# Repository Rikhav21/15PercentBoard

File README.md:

# Fifteen percent
## About
I called a fifteen percent keyboard, because it has only 32 keys in total, which is around thirty percent of a regular keyboard. Since it is a split keyboard, each *board* has around fifteen keys. I also made it as a grid, because those are supposedly better according to this one friend that I have but it is going to take like 3-4 weeks to adjust so have fun with relearning how to type!
## CAD
There is nothing really special about this, there is only a lid, and base for each. I am thinking of printing these in green, and in my opinion the renderings look pretty cool. They should be able to fit on my A1 mini, which is part of the reason why I made a split board in the first place.

## Schematic
Once again there is nothing really special. There are just the keys connected to a pico, according to rows, and columns. The picos are connected through a TRRS cable, and the right one, has a 0.96 inch OLED. I am going to have to see where I can get the TRRS cable connectors for cheaper, as right now thhe plugs seem way to overprices at 8 dollars per.

## PCB
This is just a simple PCB, I designed in Kicad.  I have all of the files in the github repo, and I am not really good at PCB design, it was my second time, which is partially why the routes are not really clean. However I do feel proud of it because it is pretty complex and I had to redo it like 3 times, and I only have 15 percent of the necassery keys.

## Firmware
I spent way to long making the firmware, because I was trying to map out the entire keyboard in my head, however this is only a standin for some better firmware later. After I actually build the board I am thinking of adding a bit more functionality, where pressing the 6 side keys could all have some cool function, and hte OLED would display what mode it was in, but for now th efirmwayre is still pretty basic until I actually make the thing.
## Matierials.
For this I will need some
- screws (m3) around 15mm
- heatset inserts m3x4x5
- Cerry MX, PCB mount keys (I want the really clicky jade ones.)
- keycaps 
- 2 raspberry picos
- 0.96 inch OLED
- Pin headers
- TRRS cable
- TRRS connectors.

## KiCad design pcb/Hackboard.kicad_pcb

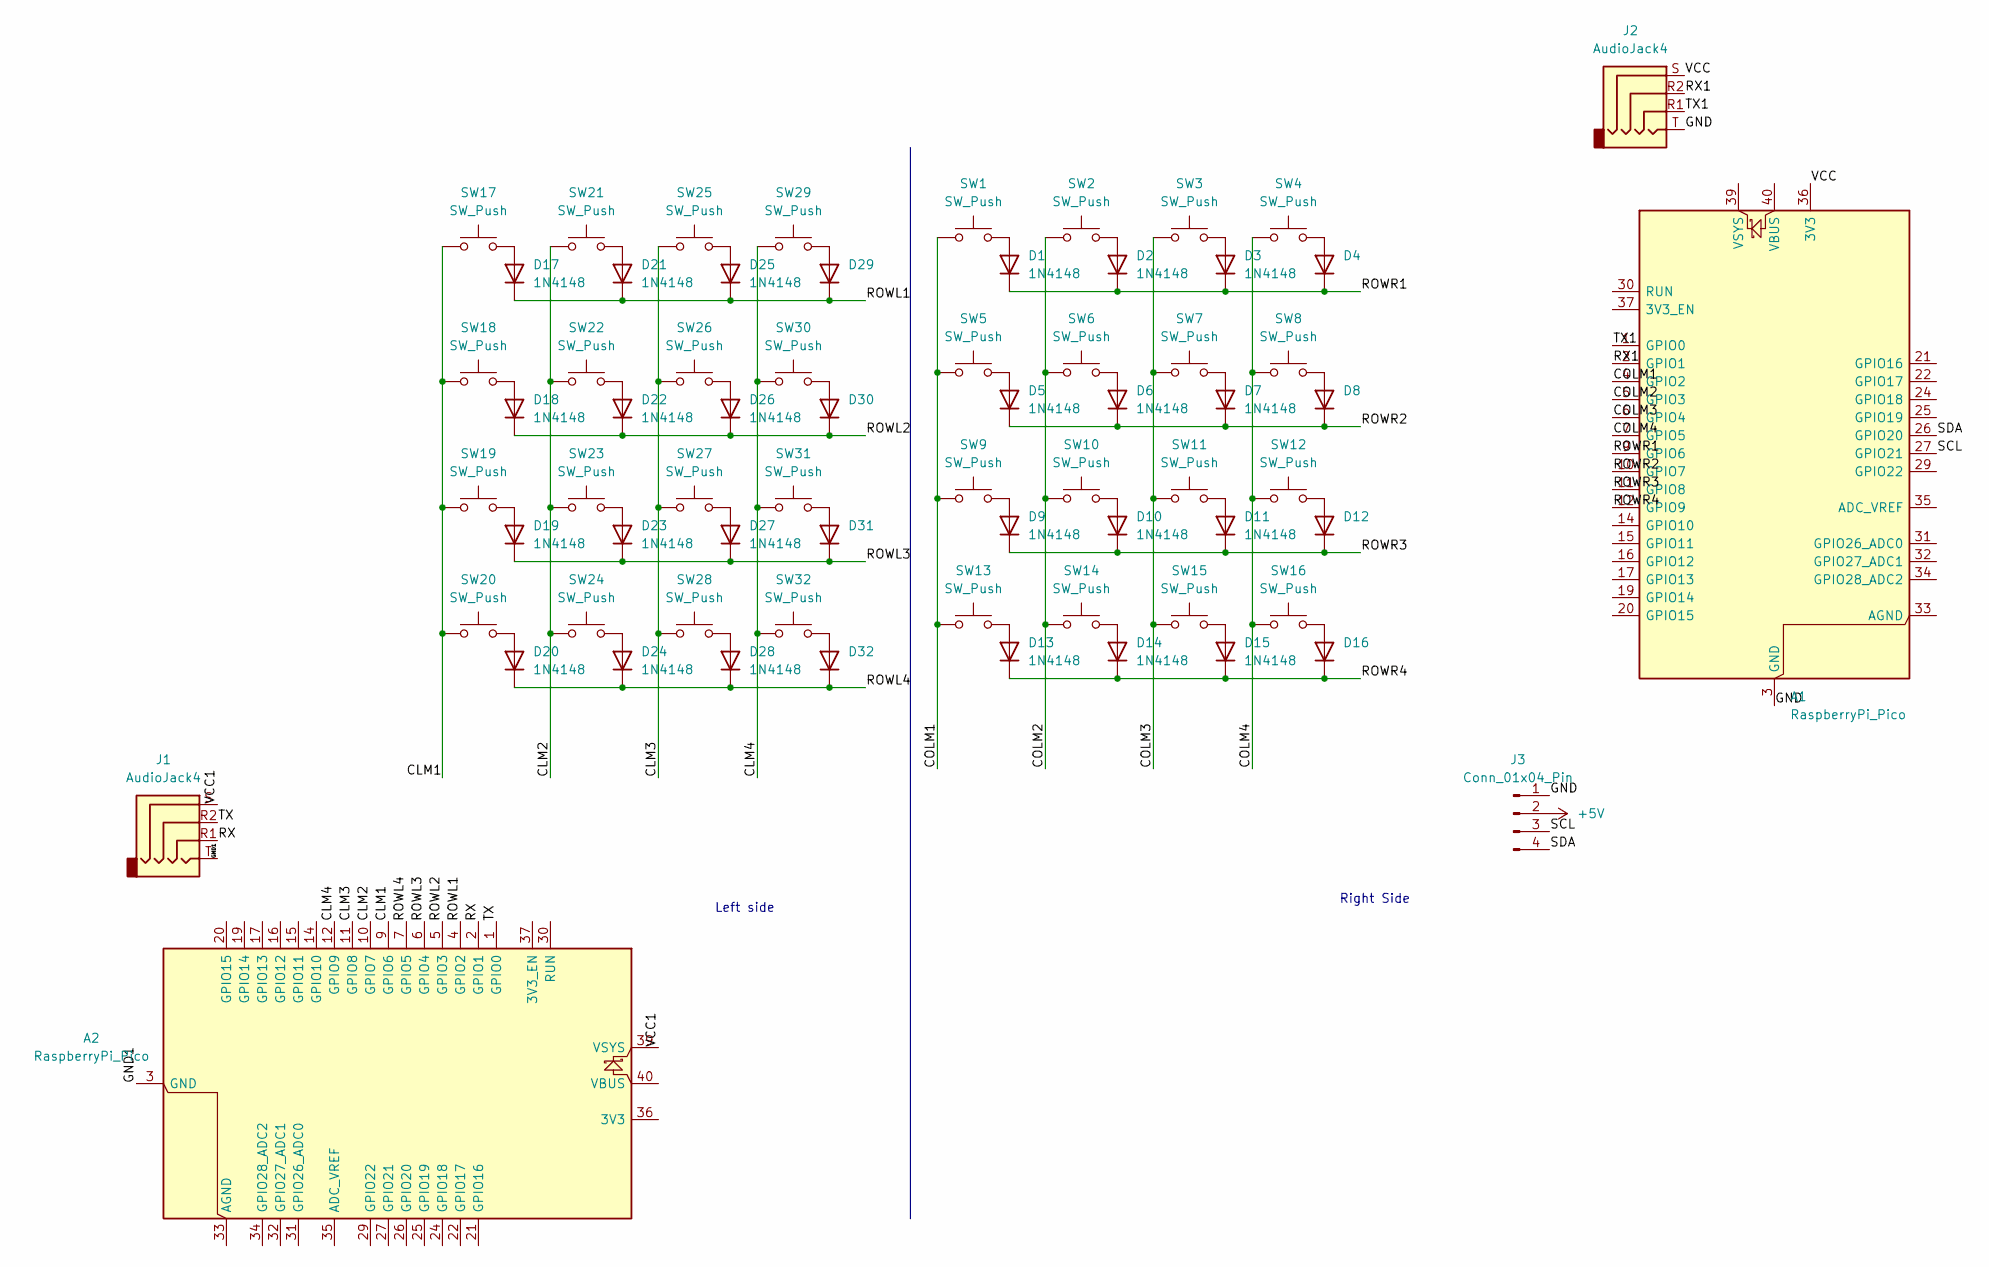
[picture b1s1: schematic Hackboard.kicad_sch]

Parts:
A1, A2: RaspberryPi_Pico; RaspberryPi_Pico_Common_Unspecified
D1, D2, D3, D4, D5, D6, D7, D8, D9, D10, D11, D12, D13, D14, D15, D16, D17, D18, D19, D20, D21, D22, D23, D24, D25, D26, D27, D28, D29, D30, D31, D32: 1N4148; D_DO-35_SOD27_P7.62mm_Horizontal
J1, J2: AudioJack4; Plug_3.5mm_CUI_SP-3541
J3: Conn_01x04_Pin; SSD1306-0.91-OLED-4pin-128x32
SW1, SW2, SW3, SW4, SW5, SW6, SW7, SW8, SW9, SW10, SW11, SW12, SW13, SW17, SW18, SW19, SW20, SW21, SW22, SW23, SW24, SW25, SW26, SW27, SW28, SW29: SW_Push; SW_Cherry_MX_1.00u_PCB
SW14, SW15, SW16, SW30, SW31, SW32: SW_Push; SW_Cherry_MX_1.50u_PCB

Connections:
+5V: J3.2
/CLM1: A2.9 (GPIO6), SW17.1, SW18.1, SW19.1, SW20.1
/CLM2: A2.10 (GPIO7), SW21.1, SW22.1, SW23.1, SW24.1
/CLM3: A2.11 (GPIO8), SW25.1, SW26.1, SW27.1, SW28.1
/CLM4: A2.12 (GPIO9), SW29.1, SW30.1, SW31.1, SW32.1
/COLM1: A1.4 (GPIO2), SW1.1, SW5.1, SW9.1, SW13.1
/COLM2: A1.5 (GPIO3), SW2.1, SW6.1, SW10.1, SW14.1
/COLM3: A1.6 (GPIO4), SW3.1, SW7.1, SW11.1, SW15.1
/COLM4: A1.7 (GPIO5), SW4.1, SW8.1, SW12.1, SW16.1
/GND: A1.3 (GND), A1.8 (GND), A1.13 (GND), A1.18 (GND), A1.23 (GND), A1.28 (GND), A1.38 (GND), J2.T, J3.1
/GND1: A2.3 (GND), A2.8 (GND), A2.13 (GND), A2.18 (GND), A2.23 (GND), A2.28 (GND), A2.38 (GND), J1.T
/ROWL1: A2.4 (GPIO2), D17.1 (K), D21.1 (K), D25.1 (K), D29.1 (K)
/ROWL2: A2.5 (GPIO3), D18.1 (K), D22.1 (K), D26.1 (K), D30.1 (K)
/ROWL3: A2.6 (GPIO4), D19.1 (K), D23.1 (K), D27.1 (K), D31.1 (K)
/ROWL4: A2.7 (GPIO5), D20.1 (K), D24.1 (K), D28.1 (K), D32.1 (K)
/ROWR1: A1.9 (GPIO6), D1.1 (K), D2.1 (K), D3.1 (K), D4.1 (K)
/ROWR2: A1.10 (GPIO7), D5.1 (K), D6.1 (K), D7.1 (K), D8.1 (K)
/ROWR3: A1.11 (GPIO8), D9.1 (K), D10.1 (K), D11.1 (K), D12.1 (K)
/ROWR4: A1.12 (GPIO9), D13.1 (K), D14.1 (K), D15.1 (K), D16.1 (K)
/RX: A2.2 (GPIO1), J1.R1
/RX1: A1.2 (GPIO1), J2.R2
/SCL: A1.27 (GPIO21), J3.3
/SDA: A1.26 (GPIO20), J3.4
/TX: A2.1 (GPIO0), J1.R2
/TX1: A1.1 (GPIO0), J2.R1
/VCC: A1.36 (3V3), J2.S
/VCC1: A2.39 (VSYS), J1.S
unnamed: D1.2 (A), SW1.2
unnamed: D2.2 (A), SW2.2
unnamed: D3.2 (A), SW3.2
unnamed: D4.2 (A), SW4.2
unnamed: D5.2 (A), SW5.2
unnamed: D6.2 (A), SW6.2
unnamed: D7.2 (A), SW7.2
unnamed: D8.2 (A), SW8.2
unnamed: D9.2 (A), SW9.2
unnamed: D10.2 (A), SW10.2
unnamed: D11.2 (A), SW11.2
unnamed: D12.2 (A), SW12.2
unnamed: D13.2 (A), SW13.2
unnamed: D14.2 (A), SW14.2
unnamed: D15.2 (A), SW15.2
unnamed: D16.2 (A), SW16.2
unnamed: D17.2 (A), SW17.2
unnamed: D18.2 (A), SW18.2
unnamed: D19.2 (A), SW19.2
unnamed: D20.2 (A), SW20.2
unnamed: D21.2 (A), SW21.2
unnamed: D22.2 (A), SW22.2
unnamed: D23.2 (A), SW23.2
unnamed: D24.2 (A), SW24.2
unnamed: D25.2 (A), SW25.2
unnamed: D26.2 (A), SW26.2
unnamed: D27.2 (A), SW27.2
unnamed: D28.2 (A), SW28.2
unnamed: D29.2 (A), SW29.2
unnamed: D30.2 (A), SW30.2
unnamed: D31.2 (A), SW31.2
unnamed: D32.2 (A), SW32.2

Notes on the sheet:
Left side
Right Side

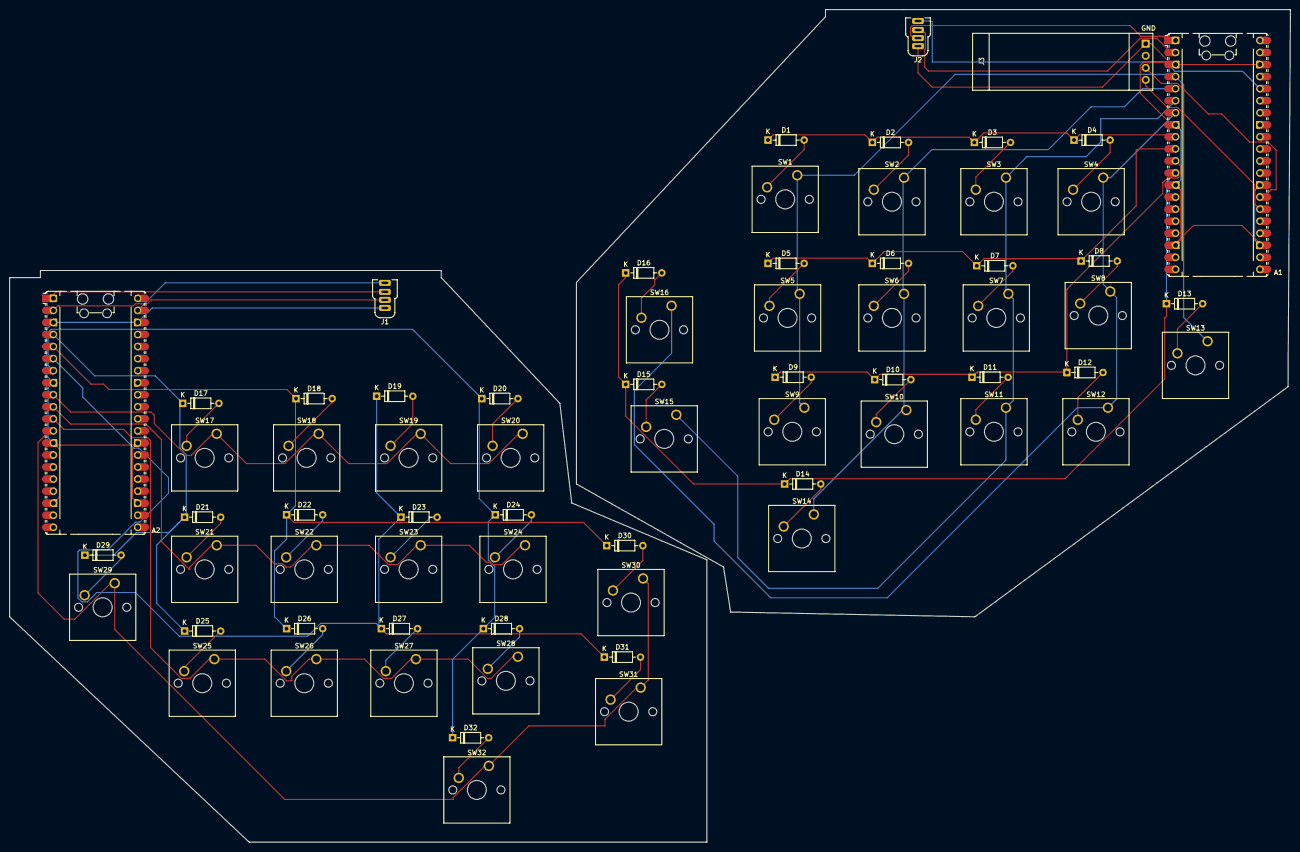
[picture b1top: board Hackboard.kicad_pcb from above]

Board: 2 copper layers, 270.0 x 175.5 mm, 69 parts (0 on the bottom side), 58 nets.

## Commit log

2025-03-10 Create LICENSE
2025-10-12 Changed how the files were arranged
2025-11-01 Rename Screenshot 2025-10-31 195831.png to CAD.png
2025-12-18 Rename Hackboard_2025-Dec-18_11-00-36PM-000_CustomizedView22336916236 (1).png to assets/CAD.png
2025-12-18 Rename Lid.stl to production/Lid.stl
2025-12-23 Rename Hackboard.step to CAD/Assembly.step
